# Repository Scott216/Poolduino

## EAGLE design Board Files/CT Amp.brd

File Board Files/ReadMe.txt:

Eagle Files Pool Controller

Outside Pool Controller - Holds Arduino Leonardo, XBee, panStamp, RTC & OLED display
Level Sensor - Transmitter for water level - holds panStamp & accelerometer
Xbee Shield - For inside pool controller which is Arduino Mega + Xbee
CT Amp - Connects to CTs measuring amps.  Uses 0-0.33 volt Current Transformers. Output is about 0-5 volts

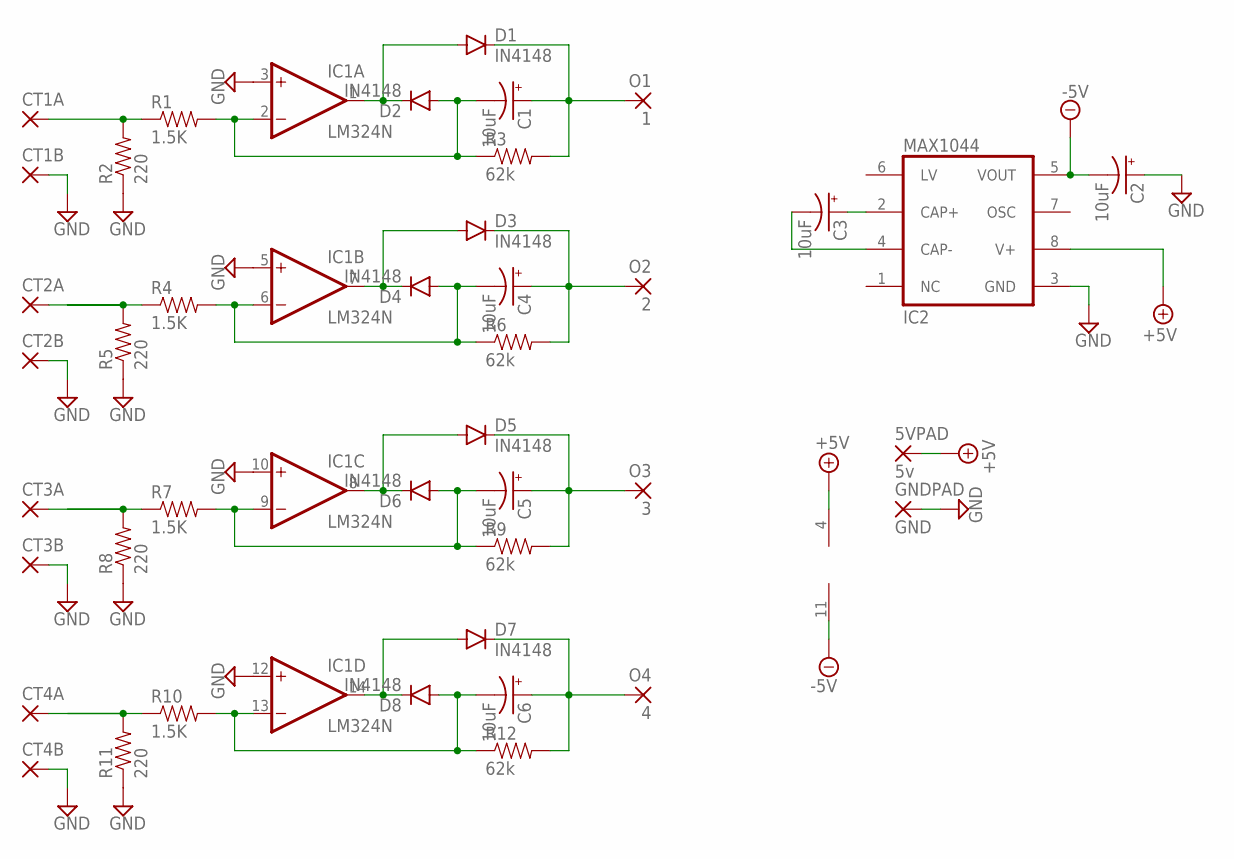
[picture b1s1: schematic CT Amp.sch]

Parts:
5VPAD: 5v; 2,54/1,0
C1, C2, C3, C4, C5, C6: 10uF; E2,5-6
CT1A, CT1B, CT2A, CT2B, CT3A, CT3B, CT4A, CT4B: 2,54/1,0
D1, D2, D3, D4, D5, D6, D7, D8: IN4148; DIODE-1N4001
GNDPAD: GND; 2,54/1,0
IC1: LM324N; DIL14
MAX1044: IC2; DIL08
O1: 1; 2,54/1,0
O2: 2; 2,54/1,0
O3: 3; 2,54/1,0
O4: 4; 2,54/1,0
R1, R4, R7, R10: 1.5K; AXIAL-0.4
R2, R5, R8, R11: 220; AXIAL-0.4
R3, R6, R9, R12: 62k; AXIAL-0.4

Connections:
+5V: 5VPAD.1, IC1.4 (V+), MAX1044.8 (V+)
-5V: C2.-, IC1.11 (V-), MAX1044.5 (VOUT)
GND: C2.+, CT1B.1, CT2B.1, CT3B.1, CT4B.1, GNDPAD.1, IC1.3 (+IN), IC1.5 (+IN), IC1.10 (+IN), IC1.12 (+IN), MAX1044.3 (GND), R2.P$1 (1), R5.P$1 (1), R8.P$1 (1), R11.P$1 (1)
unnamed: C3.+, MAX1044.2 (CAP+)
unnamed: C3.-, MAX1044.4 (CAP-)
unnamed: CT2A.1, R4.P$1 (1), R5.P$2 (2)
unnamed: C1.-, D2.A, IC1.2 (-IN), R1.P$2 (2), R3.P$1 (1)
unnamed: C5.-, D6.A, IC1.9 (-IN), R7.P$2 (2), R9.P$1 (1)
unnamed: CT3A.1, R7.P$1 (1), R8.P$2 (2)
unnamed: D1.A, D2.C, IC1.1 (OUT)
unnamed: D5.A, D6.C, IC1.8 (OUT)
unnamed: C5.+, D5.C, O3.1, R9.P$2 (2)
unnamed: C6.-, D8.A, IC1.13 (-IN), R10.P$2 (2), R12.P$1 (1)
unnamed: C4.-, D4.A, IC1.6 (-IN), R4.P$2 (2), R6.P$1 (1)
unnamed: D7.A, D8.C, IC1.14 (OUT)
unnamed: C6.+, D7.C, O4.1, R12.P$2 (2)
unnamed: C1.+, D1.C, O1.1, R3.P$2 (2)
unnamed: CT1A.1, R1.P$1 (1), R2.P$2 (2)
unnamed: CT4A.1, R10.P$1 (1), R11.P$2 (2)
unnamed: D3.A, D4.C, IC1.7 (OUT)
unnamed: C4.+, D3.C, O2.1, R6.P$2 (2)

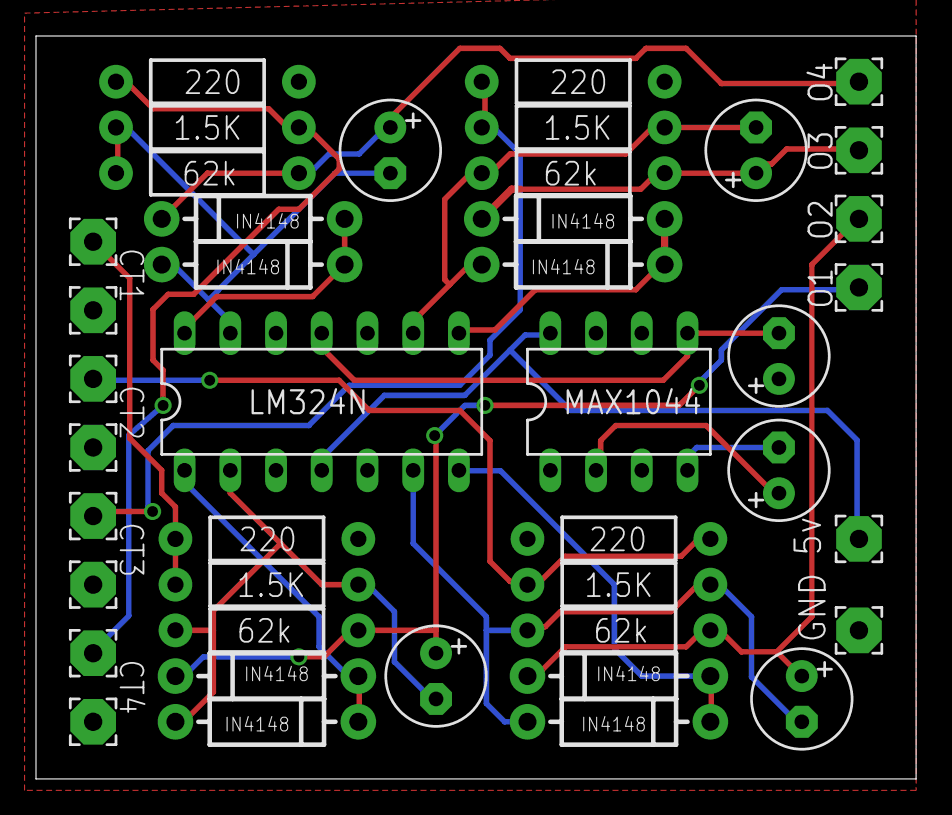
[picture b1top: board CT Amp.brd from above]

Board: 2 copper layers, 48.9 x 41.3 mm, 42 parts (0 on the bottom side), 21 nets.

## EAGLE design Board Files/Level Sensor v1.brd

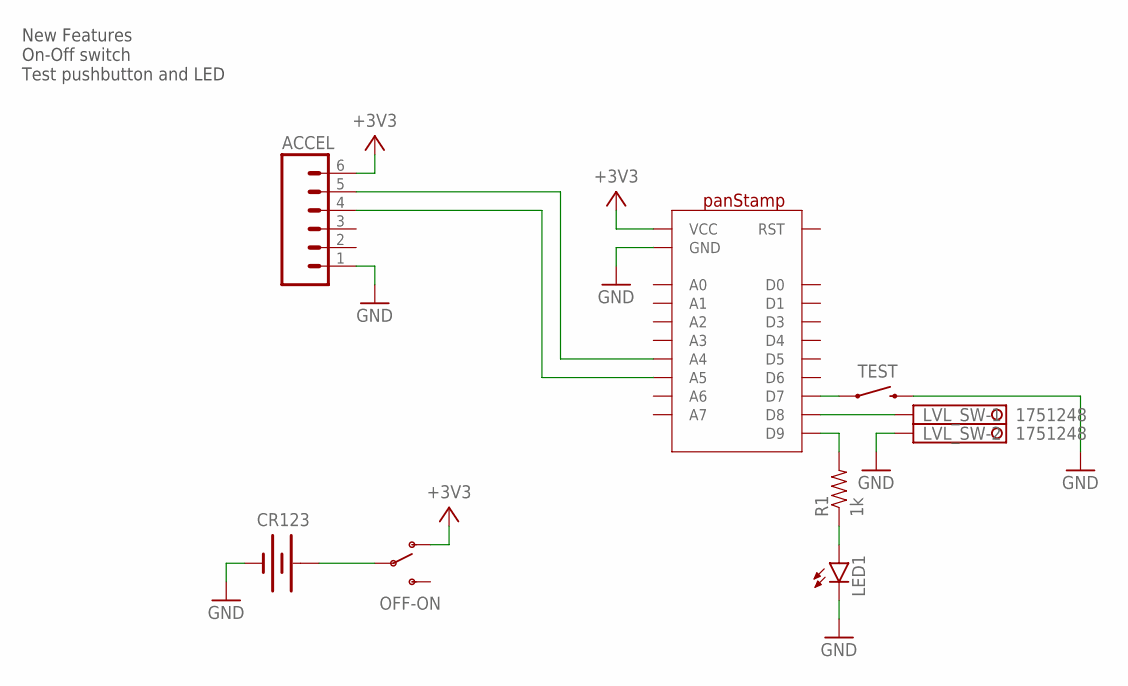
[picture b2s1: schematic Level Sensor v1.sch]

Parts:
ACCEL: M06LONGPADS; 1X06_LONGPADS
CR123: BATTERY_CR123_SINGLE; BATTERY_CR123
LED1: LED3MM
LVL_SW: 1751248
OFF-ON: SWITCH-SPDTPTH; SWITCH-SPDT
R1: 1k; AXIAL-0.4
TEST: SWITCH-MOMENTARY-2PTH; TACTILE-PTH
U$1: PANSTAMPWITH_TEXT; PANSTAMP

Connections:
+3V3: ACCEL.6, OFF-ON.1 (O), U$1.VCC
BAT+: CR123.POS (+), OFF-ON.2
GND: ACCEL.1, CR123.NEG (-), LED1.K (C), LVL_SW.2, TEST.3 (2), U$1.GND$1 (GND), U$1.GND$7 (GND), U$1.GND$15 (GND), U$1.GND$23 (GND), U$1.GND$24 (GND)
unnamed: LVL_SW.1, U$1.D8
unnamed: TEST.1, U$1.D7
unnamed: R1.P$2 (2), U$1.D9
unnamed: LED1.A, R1.P$1 (1)
SCL: ACCEL.4, U$1.A5
SDA: ACCEL.5, U$1.A4

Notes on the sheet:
New Features On-Off switch Test pushbutton and LED

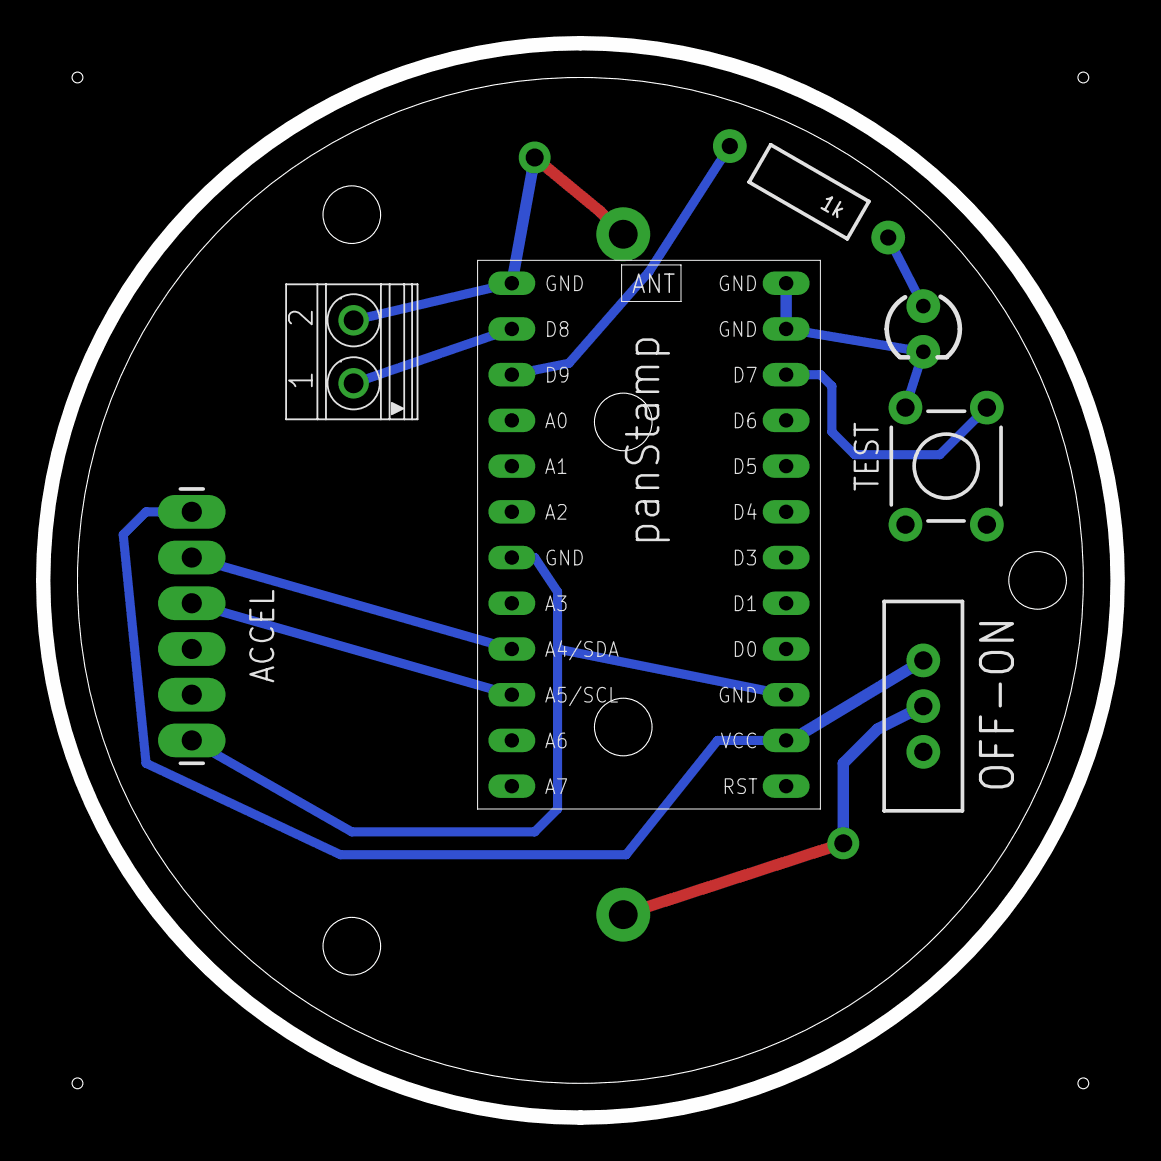
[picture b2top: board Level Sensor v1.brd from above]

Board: 2 copper layers, 59.7 x 59.7 mm, 8 parts (1 on the bottom side), 9 nets.

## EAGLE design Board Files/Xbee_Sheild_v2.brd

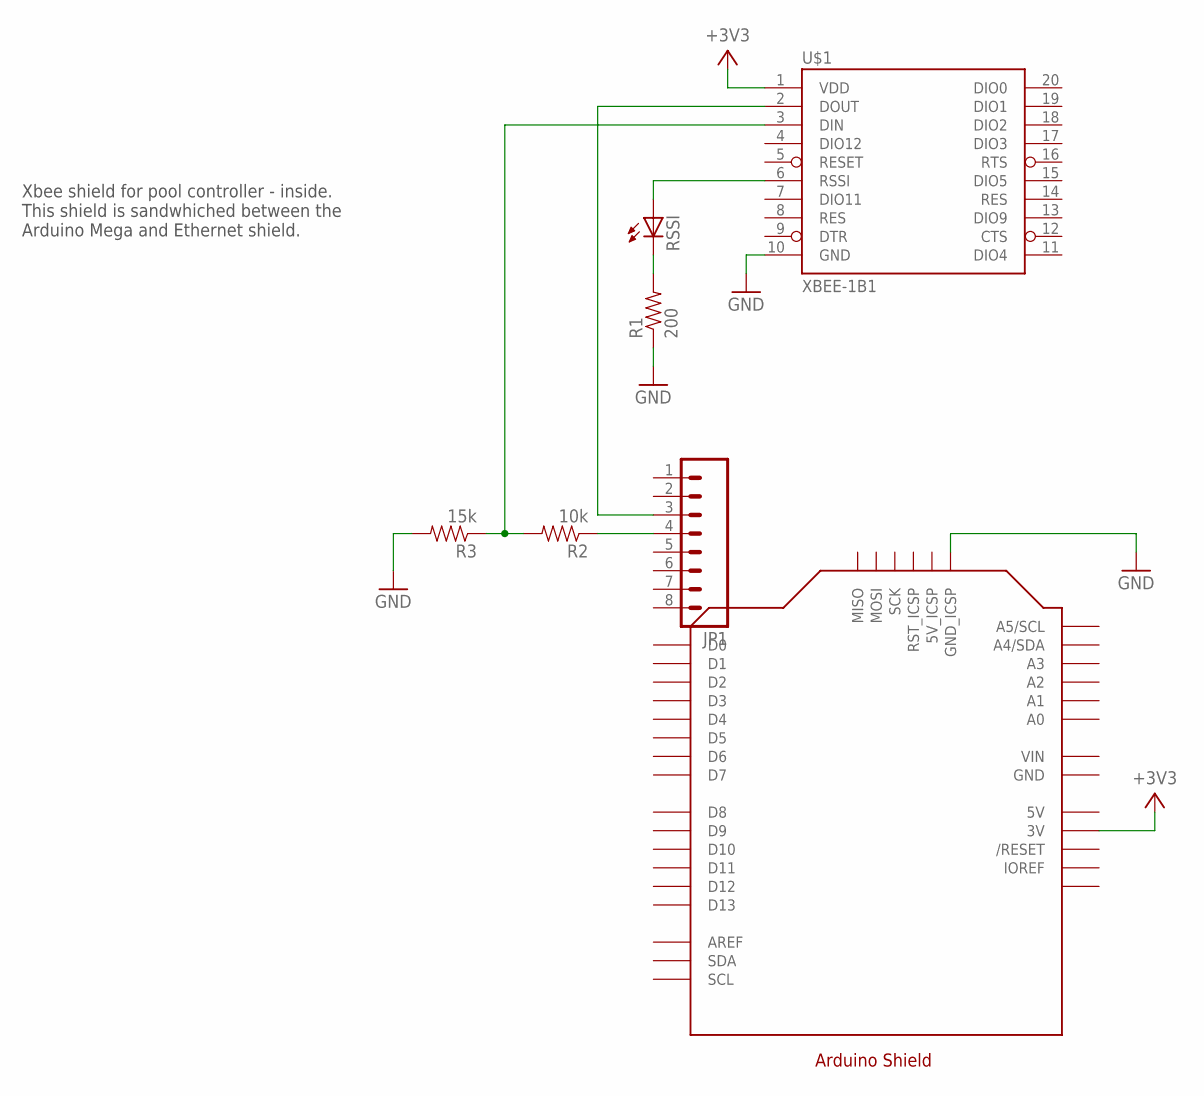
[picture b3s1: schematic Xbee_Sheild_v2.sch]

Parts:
JP1: M08LONGPADS; 1X08_LONGPADS
R1: 200; AXIAL-0.4
R2: 10k; AXIAL-0.4
R3: 15k; AXIAL-0.4
RSSI: LED5MM
U$1: XBEE-1B1; XBEE-1
U$2: ARDUINO_UNO_SHIELD_ICSP

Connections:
5V: U$2.5V@1 (5V)
5V_ICSP: U$2.5V_ICSP
+3V3: U$1.1 (VDD), U$2.3V
GND: R1.P$1 (1), R3.P$2 (2), U$1.10 (GND), U$2.GND@1 (GND), U$2.GND@2 (GND), U$2.GND@3 (GND), U$2.GND_ICSP
unnamed: JP1.3, U$1.2 (DOUT)
unnamed: JP1.4, R2.P$1 (1)
unnamed: RSSI.A, U$1.6 (RSSI)
unnamed: R1.P$2 (2), RSSI.K (C)
unnamed: R2.P$2 (2), R3.P$1 (1), U$1.3 (DIN)
VIN: U$2.VIN

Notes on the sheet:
Xbee shield for pool controller - inside. This shield is sandwhiched between the Arduino Mega and Ethernet shield.

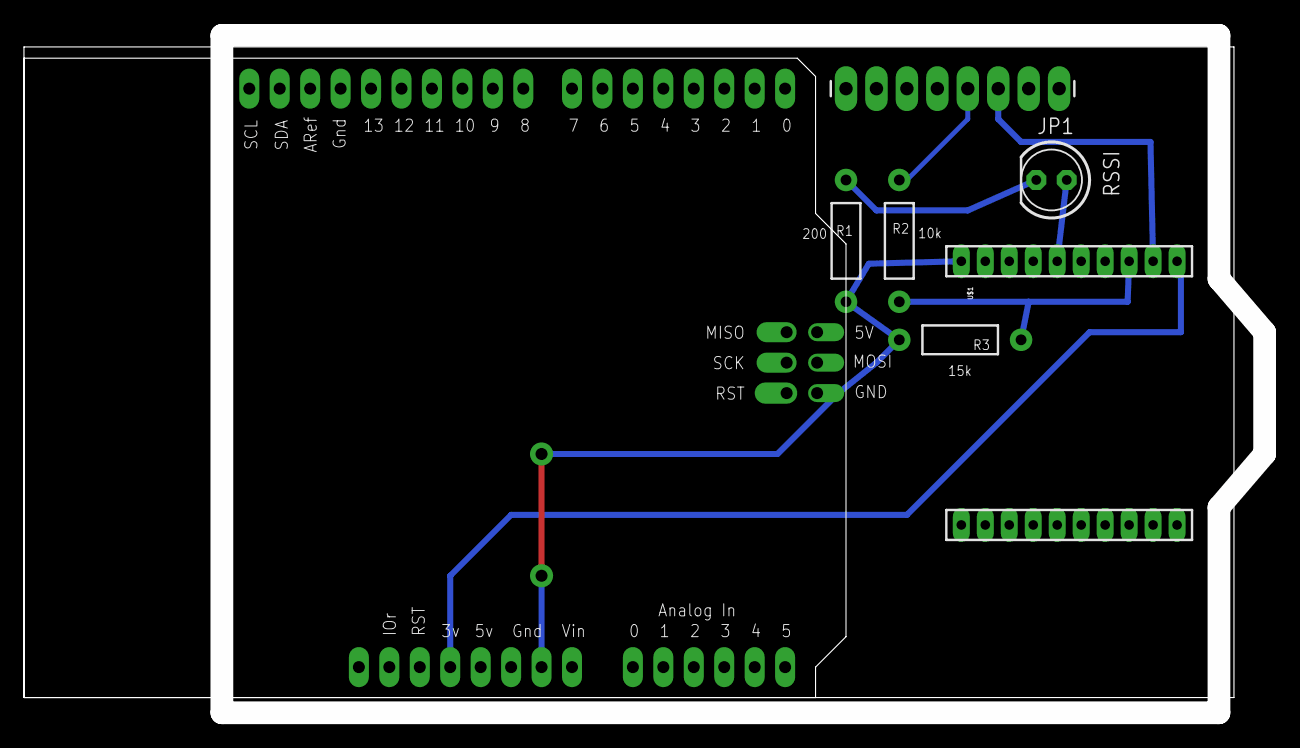
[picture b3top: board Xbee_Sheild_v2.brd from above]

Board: 2 copper layers, 102.6 x 56.5 mm, 7 parts (0 on the bottom side), 7 nets.

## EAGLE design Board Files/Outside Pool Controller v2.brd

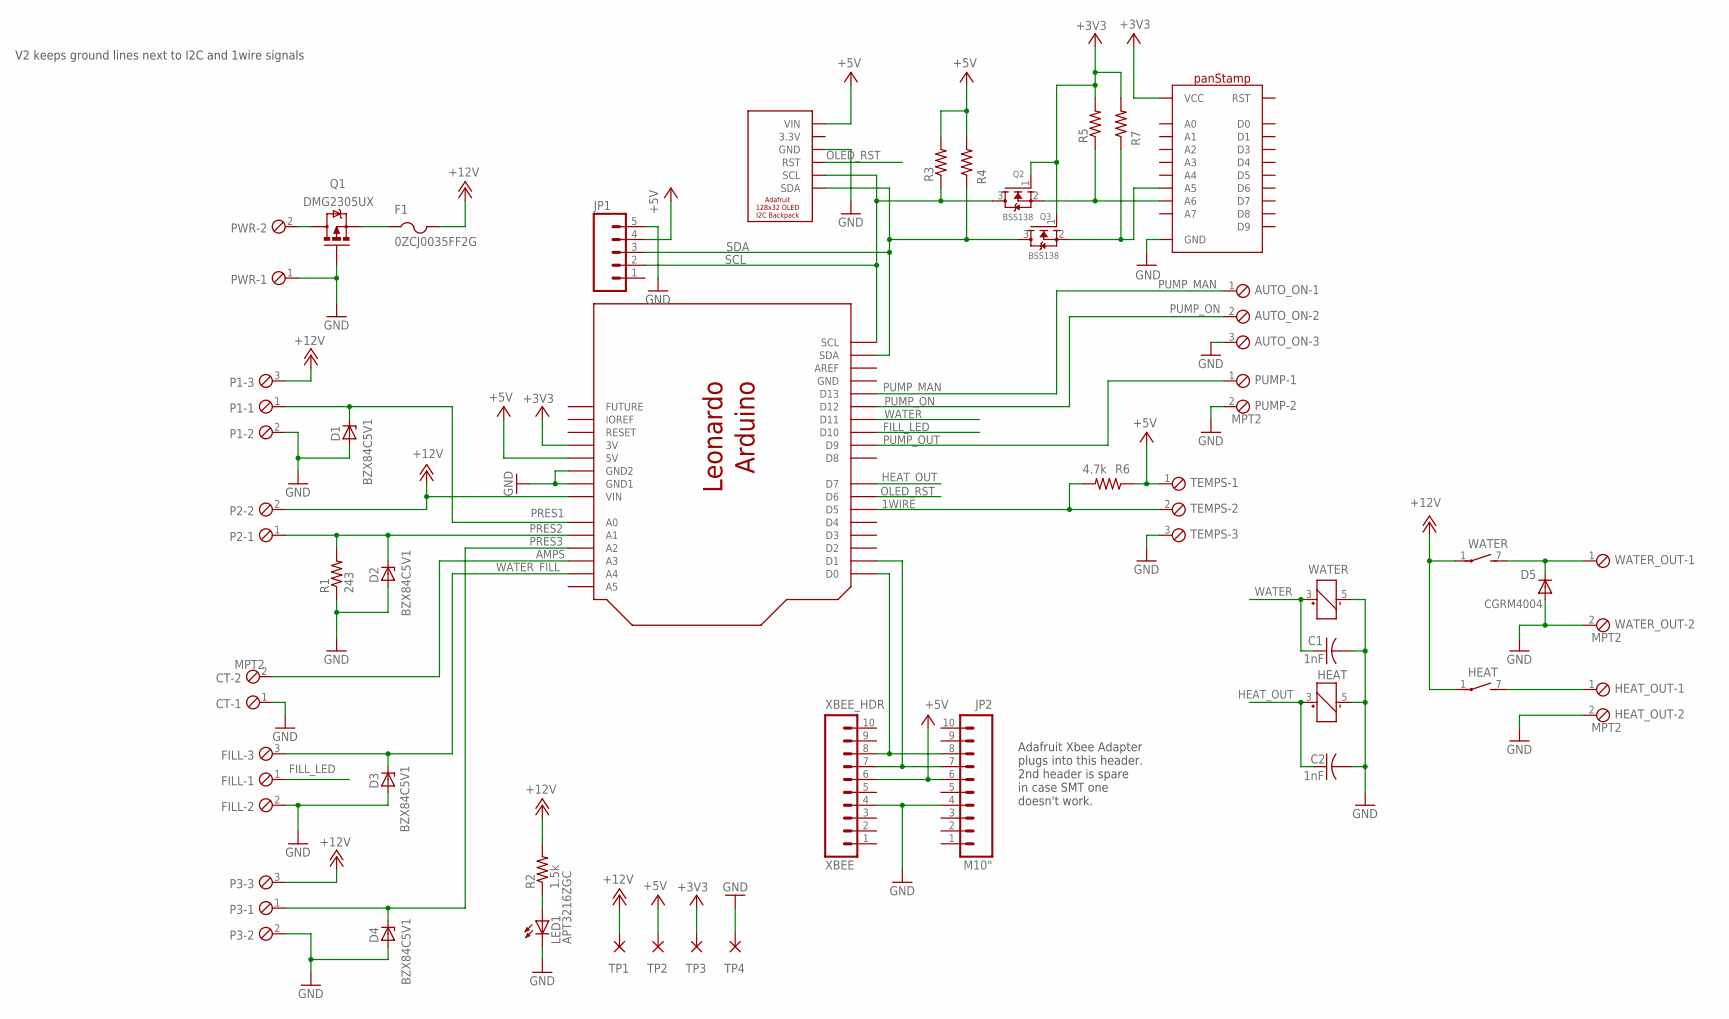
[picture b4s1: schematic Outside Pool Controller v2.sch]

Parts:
AUTO_ON: MPT3; 3POL254
C1, C2: 1nF; C1206
CT: MPT2; 2POL254
D1, D2, D3, D4: BZX84C5V1; SOT23
D5: CGRM4004; SOD-123FL
F1: 0ZCJ0035FF2G; R1206
FILL: MPT3; 3POL254
HEAT: REED
HEAT_OUT: MPT2; 2POL254
JP1: M05NO_SILK; 1X05_NO_SILK
JP2: M10"; 1X10
LED1: APT3216ZGC; CHIPLED_1206
P1, P3: MPT3; 3POL254
P2: MPT2; 2POL254
PUMP: MPT2; 2POL254
PWR: MPT2; 2POL254
Q1: DMG2305UX; SOT23-3
Q2, Q3: BSS138; SOT23
R1: 243; M1206
R2: 1.5k; M1206
R3, R4, R5, R7: R-US_M1206; M1206
R6: 4.7k; M1206
TEMPS: MPT3; 3POL254
TP1, TP2: 2,15/1,0
TP3, TP4: WIREPAD2,15/1,0; 2,15/1,0
U$1: ARDUINO_LEONARDO
U$2: ADAFRUIT_128X32_OLED; ADAFRUIT_OLED_128X32
U$3: PANSTAMPNO_TEXT; PANSTAMP_NOTEXT
WATER: REED
WATER_OUT: MPT2; 2POL254
XBEE_HDR: XBEE; 1X10_SMD_MALE

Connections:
1WIRE: R6.2, TEMPS.2, U$1.D5
3.3V: U$2.P$5 (3.3V)
+3V3: Q2.1 (G), Q3.1 (G), R5.2, R7.2, TP3.1, U$1.3V, U$3.VCC
+5V: JP1.4, JP2.6, R3.2, R4.2, R6.1, TEMPS.1, TP2.1, U$1.5V, U$2.P$6 (VIN), XBEE_HDR.6
+12V: F1.2, HEAT.1, P1.3, P2.2, P3.3, R2.2, TP1.1, U$1.VIN, WATER.1
AMPS: CT.2, U$1.A3
FILL_LED: FILL.1, U$1.D10
GND: AUTO_ON.3, C1.2, C2.2, CT.1, D1.1 (A), D2.1 (A), D3.1 (A), D4.1 (A), D5.A, FILL.2, HEAT.5 (-), HEAT_OUT.2, JP1.5, JP2.4, LED1.C, P1.2, P3.2, PUMP.2, PWR.1, Q1.1 (G), R1.1, TEMPS.3, TP4.1, U$1.GND, U$1.GND$2 (GND2), U$1.GND$3 (GND1), U$2.P$4 (GND), U$3.GND$1 (GND), U$3.GND$7 (GND), U$3.GND$15 (GND), U$3.GND$23 (GND), U$3.GND$24 (GND), WATER.5 (-), WATER_OUT.2, XBEE_HDR.4
HEAT_OUT: C2.1, HEAT.3 (+), U$1.D7
unnamed: D5.C, WATER.7 (S), WATER_OUT.1
unnamed: HEAT.7 (S), HEAT_OUT.1
unnamed: PWR.2, Q1.3 (D)
unnamed: LED1.A, R2.1
unnamed: F1.1, Q1.2 (S)
OLED_RST: U$1.D6, U$2.P$3 (RST)
PRES1: D1.3 (C), P1.1, U$1.A0
PRES2: D2.3 (C), P2.1, R1.2, U$1.A1
PRES3: D4.3 (C), P3.1, U$1.A2
PUMP_MAN: AUTO_ON.1, U$1.D13
PUMP_ON: AUTO_ON.2, U$1.D12
PUMP_OUT: PUMP.1, U$1.D9
SCL: JP1.2, Q2.3 (D), R3.1, U$1.SCL, U$2.P$2 (SCL)
SCL3.3: Q2.2 (S), R5.1, U$3.A6
SDA: JP1.3, Q3.3 (D), R4.1, U$1.SDA, U$2.P$1 (SDA)
SDA3.3: Q3.2 (S), R7.1, U$3.A5
WATER: C1.1, U$1.D11, WATER.3 (+)
WATER_FILL: D3.3 (C), FILL.3, U$1.A4
XBEE0: JP2.8, U$1.D0, XBEE_HDR.8
XBEE1: JP2.7, U$1.D1, XBEE_HDR.7

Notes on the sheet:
V2 keeps ground lines next to I2C and 1wire signals
Adafruit Xbee Adapter plugs into this header. 2nd header is spare in case SMT one doesn't work.

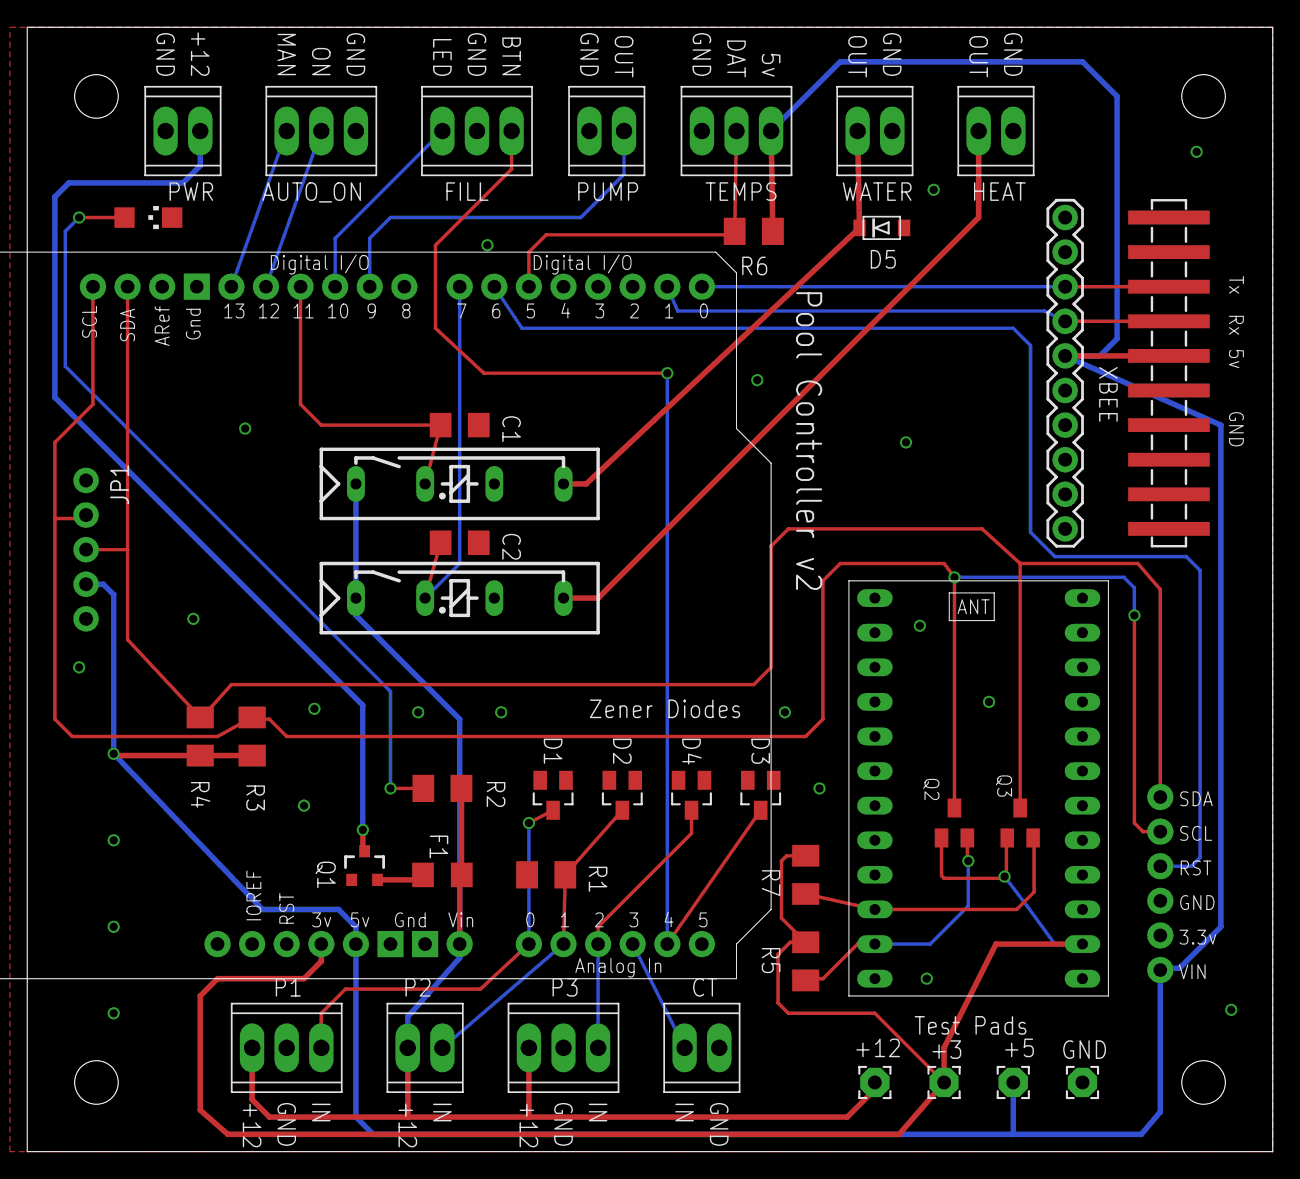
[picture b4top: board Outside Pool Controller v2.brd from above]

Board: 2 copper layers, 91.4 x 82.5 mm, 42 parts (0 on the bottom side), 28 nets.

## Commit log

2013-08-01 added tweet for pump on at night
2013-08-20 small changes
2013-08-21 rewrote how sensors are read. Added support for for 100 PSI sensor
2013-08-21 removed maincpp.txt
2013-09-05 fixed bug in pressure cutoff and pump amps
2013-09-05 fixed bug in water fill pressure
2013-09-15 put alarm tweets in separate function. Made PoolData[] global
2013-09-15 formatting
2013-09-16 more data from water level sensor
2013-09-17 added alerts for heater on and sensor trouble
2013-09-18 changed some of #define to const
2013-09-19 added time.h library to inside controller
2013-12-27 Tweeks to datalogging
2014-01-24 EmbedXcode+ upgrade
    Changes related to EmbedXcode upgrade
2014-06-04 Various
    Added alert for pump off in the day. Put array elements in enum().
    Changed xbee.begin(),
2014-06-04 changed xbee.begin()
    changes from xbee.begin(9600), to xbee.begin(Serial)
2014-06-23 v1.50. Fixed alerts
    Added missing resets to some of the twitter flags (tf_). Got rid of
    multiple alerts at 11PM. Added functions for sensor status. Don't
    upload streams to xively if sensor is bad or data is invalid.
2014-06-24 v1.52 SD card
    If sensor isn't working, sent n/a to SD card instead of last known value
2014-06-26 delay in pump off
    Pump off delay to prevent false positive for current sensor status
2014-06-26 Added bitty URL to tweet
2014-06-27 fixed overflow bug
    Fixed char overflow, removed pooltime from sendTweet() function. When
    alarm is triggered, record will be saved to SD card. Changed Xbee
    timeout from 5 min to 30 sec
2014-07-02 Fixed to work with new xbee library
2014-08-03 v1.58 - fixed false positive for alarm
    Put a delay in sending tweets. Alarm must still be active after 2
    seconds in order for tweet to be sent
2014-08-03 Changed water fill max time
    Changed daily max from 120 minutes to 60.
2014-08-07 moved a couple variables around
    Removed a couple global variables
2014-08-07 Minor formatting
2014-08-07 v1.55 - changed water added minutes
    tracking of minutes of water added was in 15 minute chunks, now it’s 1
    minute chunks
2014-08-18 v1.59 Switched to Serial1 for Xbee, log lid is level
    Using Serial1 for Xbee. Logging if water level lid is level
2014-08-18 v1.56 added checksum, monitor is lid level
2014-08-18 Added checksum
2014-08-18 Switched water fill countdown with Is Lid Level
2014-08-18 Changed panstamp ok from 0 to 1
    Testing with water level sensor disconnected, about 10% of the time the
    sensor status byte said the level sensor was online. There are a lot
    of checksum errors on the I2C - all the data was zero except checksum.
    Zero is a valid value for the panstamp being online, so I changed it to
    a 1.
2014-09-03 Added pushbutton test and LED
2014-09-03 made constants upper case
2014-09-04 Initial Commit for Eagle files
    PCB files designed in Eagle 6.5
2014-09-14 v1.61 - water fill alert, fixed bug in xbee data
2014-09-14 v1.58 - increased max water fill time
    Also changed some constants
2015-01-04 v1.65 varios minor changes
2015-01-04 Deleted
2015-01-04 v1.60 various changes, see change log
2015-01-04 Changes to comments
2015-06-21 v1.67 Updated tweet
2015-06-21 v1.63 OLED display, Low pressure
    Added code for OLED display, Reset low pressure alarm at midnight, code
    to detect pressure sensor failure
2015-06-21 v1.13 panstamp v2 API
2015-07-06 v1.68 changed NTP server
2015-07-10 v1.70 - fixed alert for water fill, changed time server
2015-07-12 v1.71 added Time_NTP.h library. 30 min delay to level sensor apart
2015-09-02 v1.64 - fixed low press alarm bug
    Also added #ifdef around OLED code to reduce program size
2015-09-02 v1.73 fixed xbee alert, adjusted EST time offset
2016-02-15 CT Amp schematic
2016-04-02 v2 - Rerouted PCB
    Original board had some problems, so I rerouted the traces
2016-06-18 v1.65 prints time in setup()
2016-06-18 v1.74 - undid v1.73. Was causing reboots

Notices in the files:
parts and their libraries:
SparkFun-Resistors: Licensing: Creative Commons ShareAlike 4.0 International - https://creativecommons.org/licenses/by-sa/4.0
